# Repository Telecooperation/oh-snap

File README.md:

<h1 align="center">Oh, Snap!</h1>
<p align="center">A Fabrication Pipeline to Magnetically Connect Conventional and 3D-Printed Electronics.</p>

<div align="center">

  <br />
    <!--<a href="https://github.com/othneildrew/Best-README-Template"><strong>Explore the docs »</strong></a>
    <br />
    <br />-->
  <h4 align="center">
    <a href="https://www.youtube.com/watch?v=JX3ZwKnnJVs">Watch Teaser</a>
    ·
    <a href="/assets/Schmitz2021-OhSnap.pdf">View PDF</a>
    ·
    <a href="https://www.youtube.com/watch?v=0AUrrtwaPVQ">Watch Talk</a>
    ·
    <a href="https://doi.org/10.1145/3411764.3445641">Follow DOI</a>
    </h4>
</div>

## Paper Abstract
3D printing has revolutionized rapid prototyping by speeding up the creation of custom-shaped objects. With the rise of multi-material 3D printers, these custom-shaped objects can now be made interactive in a single pass through passive conductive structures. However, connecting conventional electronics to these conductive structures often still requires time-consuming manual assembly involving many wires, soldering or gluing.

To alleviate these shortcomings, we propose <i>Oh, Snap!</i>: a fabrication pipeline and interfacing concept to magnetically connect a 3D-printed object equipped with passive sensing structures to conventional sensing electronics. To this end, <i>Oh, Snap!</i> utilizes ferromagnetic and conductive 3D-printed structures, printable in a single pass on standard printers. We further present a proof-of-concept capacitive sensing board that enables easy and robust magnetic assembly to quickly create interactive 3D-printed objects. We evaluate <i>Oh, Snap!</i> by assessing the robustness and quality of the connection and demonstrate its broad applicability by a series of example applications.

## How to use
We provide the schematics and firmware for the Oh, Snap board for capacitive sensing, as well as sample code and 3D models used for the example applications in the paper.

### Schematics
The [schematics](/schematics/) folder contains all schematics to clone the presented Oh, Snap board or use them as a basis for another kind of board. The schematics are provided in Eagle format.

### Firmware
The [firmware](/firmware/) folder contains the firmware required to operate the Oh, Snap board. Please see [firmware/README.md](/firmware/README.md) for more details on the flashing procedure.

### Example Applications

The [examples](/examples/) folder contains code for some example applications:
- [Car Gesture](examples/gesture) (A)
- [Flowerpot](examples/flowerpot) (B)
- [Smarthome Control](examples/smarthome) (C)
- [Piano](examples/piano)

In addition, it also contains some simple monitoring demos.

### 3D Models
For the 3D models used for the example applications and the evaluation see [here](models/).

## How to cite
Please cite this work like this:
<pre>
  Martin Schmitz, Jan Riemann, Florian Müller, Steffen Kreis, and Max Mühlhäuser. 2021. 
  Oh, Snap! A Fabrication Pipeline to Magnetically Connect Conventional and 3D-Printed Electronics. 
  In Proceedings of the 2021 CHI Conference on Human Factors in Computing Systems (CHI ’21), 1–11. 
  https://doi.org/10.1145/3411764.3445641
  </pre>

or use this

<pre>
@inproceedings{10.1145/3411764.3445641,
author = {Schmitz, Martin and Riemann, Jan and M\"{u}ller, Florian and Kreis, Steffen and M\"{u}hlh\"{a}user, Max},
title = {Oh, Snap! A Fabrication Pipeline to Magnetically Connect Conventional and 3D-Printed Electronics},
year = {2021},
isbn = {9781450380966},
publisher = {Association for Computing Machinery},
address = {New York, NY, USA},
url = {https://doi.org/10.1145/3411764.3445641},
doi = {10.1145/3411764.3445641},
booktitle = {Proceedings of the 2021 CHI Conference on Human Factors in Computing Systems},
articleno = {420},
numpages = {11},
keywords = {capacitive sensing, proximity, touch, prototyping, 3D printing},
location = {Yokohama, Japan},
series = {CHI '21}
}
</pre>

## Credits
This project uses the following sources:
- [Protocentral FDC1004](https://github.com/Protocentral/ProtoCentral_fdc1004_breakout)
- [ESPAsyncWebServer](https://github.com/me-no-dev/ESPAsyncWebServer)
- [MQTT PubSubClient](https://github.com/knolleary/pubsubclient)
- [ArduinoJSON]( https://github.com/bblanchon/ArduinoJson)
- [FreeRTOS]( https://github.com/FreeRTOS/FreeRTOS)
- [Tone.js]( https://github.com/Tonejs/Tone.js)
- [Plotly.js](https://github.com/plotly/plotly.js)
- [Arduino-ESP32](https://github.com/espressif/arduino-esp32)
- [Logo](https://www.pngaaa.com/detail/1826967)

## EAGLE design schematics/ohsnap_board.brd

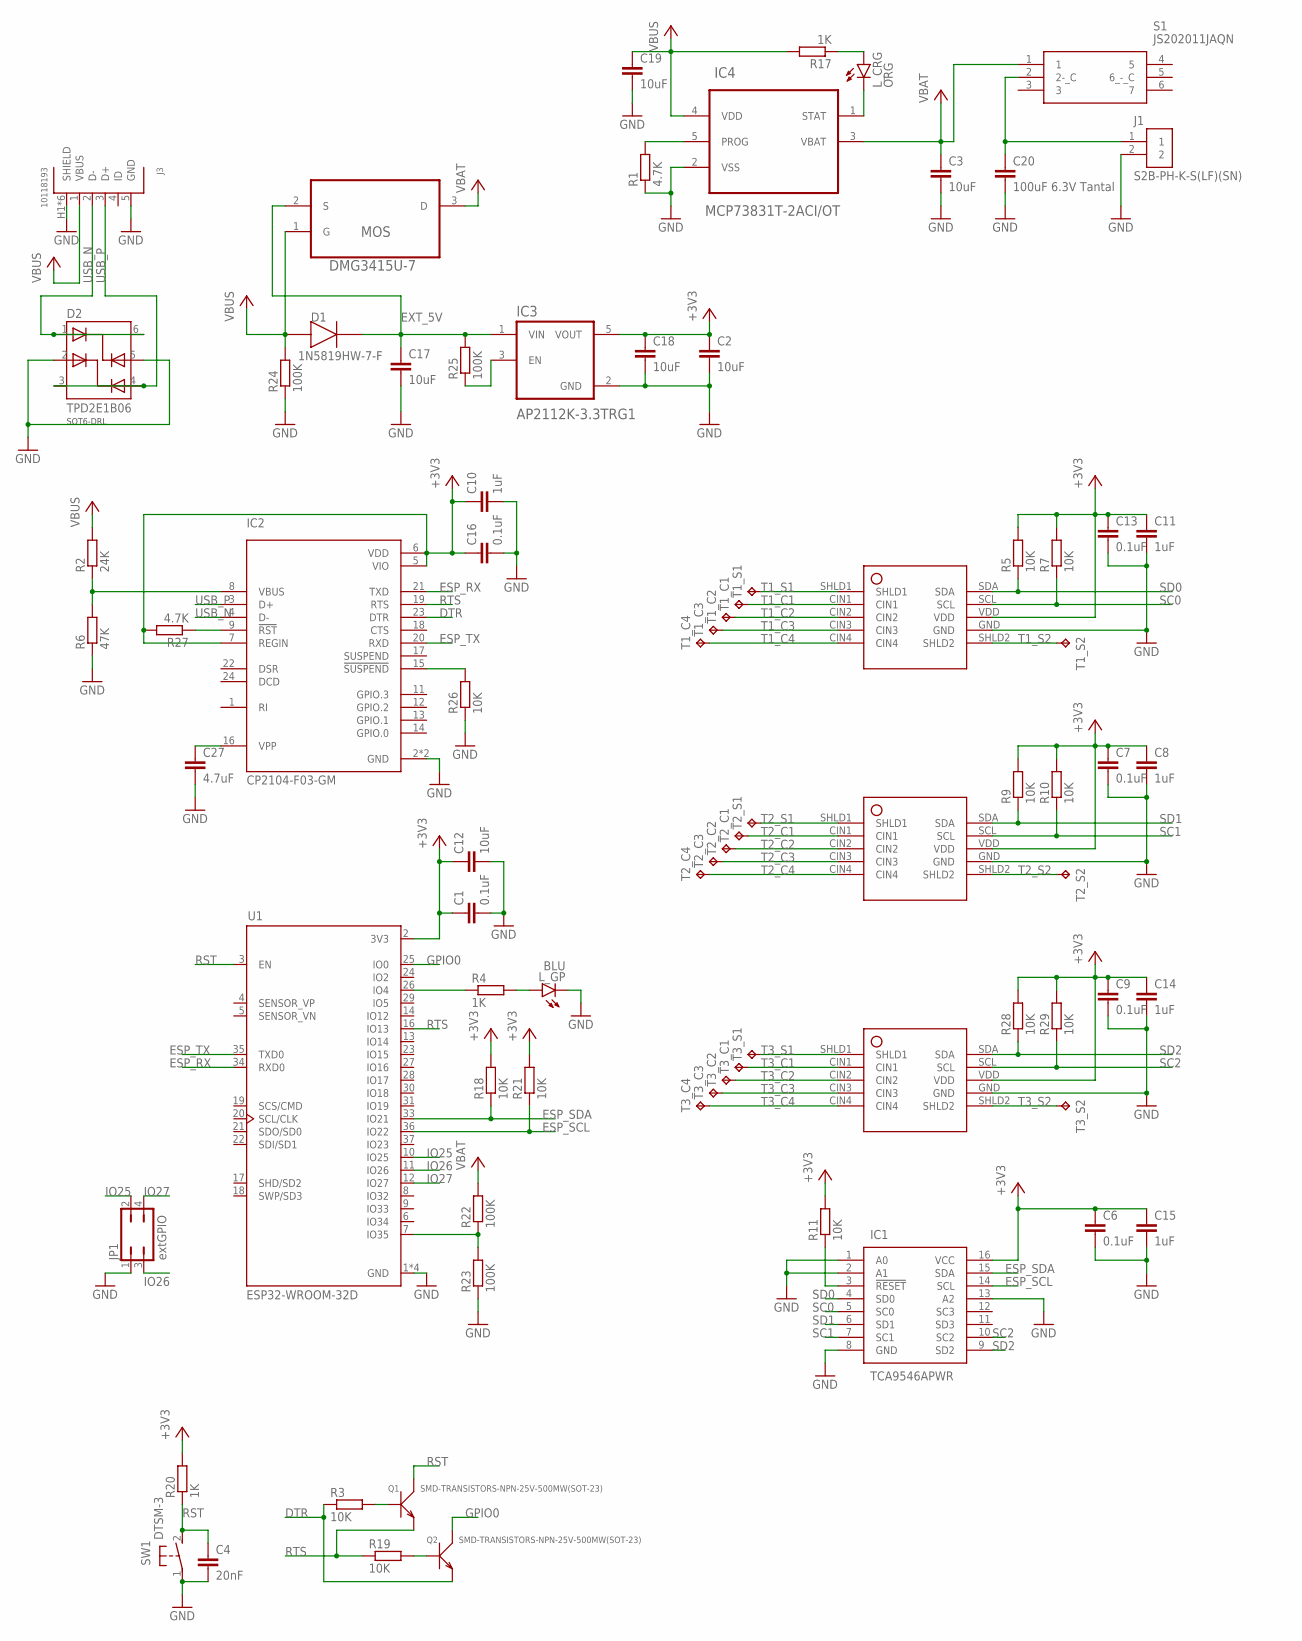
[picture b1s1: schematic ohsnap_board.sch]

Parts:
C1, C6, C7, C9, C13, C16: 0.1uF; C0603
C2, C3, C12, C17, C18, C19: 10uF; C0805
C4: 20nF; C0603
C8, C10, C11, C14, C15: 1uF; C0603
C20: 100uF 6.3V Tantal; C0805
C27: 4.7uF; C0805
D1: 1N5819HW-7-F; SOD370155X135
D2: TPD2E1B06; SOT6-DRL
IC1: TCA9546APWR; SOP65P640X120-16N
IC2: CP2104-F03-GM; QFN50P400X400X80-25N
IC3: AP2112K-3.3TRG1; SOT95P285X140-5N
IC4: MCP73831T-2ACI/OT; SOT95P280X145-5N
IC5, IC6, IC7: FDC1004_SOP10; SOP50P490X109-10N
J1: S2B-PH-K-S(LF)(SN); JST_S2B-PH-K-S(LF)(SN)
J3: 10118193
JP1: extGPIO; JP2Q
L_CRG: ORG; SML0603
L_GP: BLU; SML0603
MOS: DMG3415U-7; SOT95P240X105-3N
Q1, Q2: SMD-TRANSISTORS-NPN-25V-500MW(SOT-23); SOT-23
R1, R27: 4.7K; R0603
R2: 24K; R0603
R3, R5, R7, R9, R10, R11, R18, R19, R21, R26, R28, R29: 10K; R0603
R4, R17, R20: 1K; R0603
R6: 47K; R0603
R22, R23, R24, R25: 100K; R0603
S1: JS202011JAQN
SW1: DTSM-3
T1_C1, T1_C2, T1_C3, T1_C4, T2_C1, T2_C2, T2_C3, T2_C4, T3_C1, T3_C2, T3_C3, T3_C4: TPB2,54; B2,54
T1_S1: T1_S1; B2,54
T1_S2: T1_SHLD2; B2,54
T2_S1: T2_SHLD1; B2,54
T2_S2: T2_SHLD2; B2,54
T3_S1: T3_SHLD1; B2,54
T3_S2: T3_S2; B2,54
U1: ESP32-WROOM-32D; MODULE_ESP32-WROOM-32D

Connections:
+3V3: C1.1, C2.1, C6.1, C7.1, C8.1, C9.1, C10.1, C11.1, C12.1, C13.1, C14.1, C15.1, C16.1, C18.1, IC1.16 (VCC), IC2.5 (VIO), IC2.6 (VDD), IC2.7 (REGIN), IC3.5 (VOUT), IC5.VDD, IC6.VDD, IC7.VDD, R5.2, R7.2, R9.2, R10.2, R11.2, R18.2, R20.2, R21.2, R27.2, R28.2, R29.2, U1.2 (3V3)
DTR: IC2.23 (DTR), Q2.2 (E), R3.1
ESP_RX: IC2.21 (TXD), U1.34 (RXD0)
ESP_SCL: IC1.14 (SCL), R21.1, U1.36 (IO22)
ESP_SDA: IC1.15 (SDA), R18.1, U1.33 (IO21)
ESP_TX: IC2.20 (RXD), U1.35 (TXD0)
EXT_5V: C17.1, D1.1 (C), IC3.1 (VIN), MOS.2 (S), R25.2
GND: C1.2, C2.2, C3.2, C4.2, C6.2, C7.2, C8.2, C9.2, C10.2, C11.2, C12.2, C13.2, C14.2, C15.2, C16.2, C17.2, C18.2, C19.2, C20.2, C27.2, D2.2 (IOB1), D2.5 (IOA2), IC1.1 (A0), IC1.2 (A1), IC1.8 (GND), IC1.13 (A2), IC2.2 (GND), IC2.25 (GND), IC3.2 (GND), IC4.2 (VSS), IC5.GND, IC6.GND, IC7.GND, J1.2, J3.5 (GND), J3.H1 (SHIELD), J3.H2 (SHIELD), J3.S1 (SHIELD), J3.S2 (SHIELD), J3.S3 (SHIELD), J3.S4 (SHIELD), JP1.1, L_GP.C, R1.1, R6.1, R23.1, R24.1, R26.1, SW1.1, U1.1 (GND), U1.15 (GND), U1.38 (GND), U1.39 (GND)
GPIO0: Q2.3 (C), U1.25 (IO0)
IO25: JP1.2, U1.10 (IO25)
IO26: JP1.3, U1.11 (IO26)
IO27: JP1.4, U1.12 (IO27)
unnamed: L_GP.A, R4.2
unnamed: R4.1, U1.26 (IO4)
unnamed: IC3.3 (EN), R25.1
unnamed: R22.1, R23.2, U1.7 (IO35)
unnamed: C20.1, J1.1, S1.2 (2-_C)
unnamed: IC2.15 (!SUSPEND), R26.2
unnamed: C27.1, IC2.16 (VPP)
unnamed: IC2.8 (VBUS), R2.1, R6.2
unnamed: IC2.9 (!RST), R27.1
unnamed: Q1.1 (B), R3.2
unnamed: Q2.1 (B), R19.2
unnamed: IC1.3 (!RESET), R11.1
unnamed: IC4.1 (STAT), L_CRG.C
unnamed: L_CRG.A, R17.1
unnamed: IC4.5 (PROG), R1.2
RST: C4.1, Q1.3 (C), R20.1, SW1.2, U1.3 (EN)
RTS: IC2.19 (RTS), Q1.2 (E), R19.1, U1.16 (IO13)
SC0: IC1.5 (SC0), IC5.SCL, R7.1
SC1: IC1.7 (SC1), IC6.SCL, R10.1
SC2: IC1.10 (SC2), IC7.SCL, R29.1
SD0: IC1.4 (SD0), IC5.SDA, R5.1
SD1: IC1.6 (SD1), IC6.SDA, R9.1
SD2: IC1.9 (SD2), IC7.SDA, R28.1
T1_C1: IC5.CIN1, T1_C1.TP
T1_C2: IC5.CIN2, T1_C2.TP
T1_C3: IC5.CIN3, T1_C3.TP
T1_C4: IC5.CIN4, T1_C4.TP
T1_S1: IC5.SHLD1, T1_S1.TP
T1_S2: IC5.SHLD2, T1_S2.TP
T2_C1: IC6.CIN1, T2_C1.TP
T2_C2: IC6.CIN2, T2_C2.TP
T2_C3: IC6.CIN3, T2_C3.TP
T2_C4: IC6.CIN4, T2_C4.TP
T2_S1: IC6.SHLD1, T2_S1.TP
T2_S2: IC6.SHLD2, T2_S2.TP
T3_C1: IC7.CIN1, T3_C1.TP
T3_C2: IC7.CIN2, T3_C2.TP
T3_C3: IC7.CIN3, T3_C3.TP
T3_C4: IC7.CIN4, T3_C4.TP
T3_S1: IC7.SHLD1, T3_S1.TP
T3_S2: IC7.SHLD2, T3_S2.TP
USB_N: D2.1 (IOA1), D2.6 (NC), IC2.4 (D-), J3.2 (D-)
USB_P: D2.3 (NC), D2.4 (IOB2), IC2.3 (D+), J3.3 (D+)
VBUS: C19.1, D1.2 (A), IC4.4 (VDD), J3.1 (VBUS), MOS.1 (G), R2.2, R17.2, R24.2
VCC: C3.1, IC4.3 (VBAT), MOS.3 (D), R22.2, S1.1

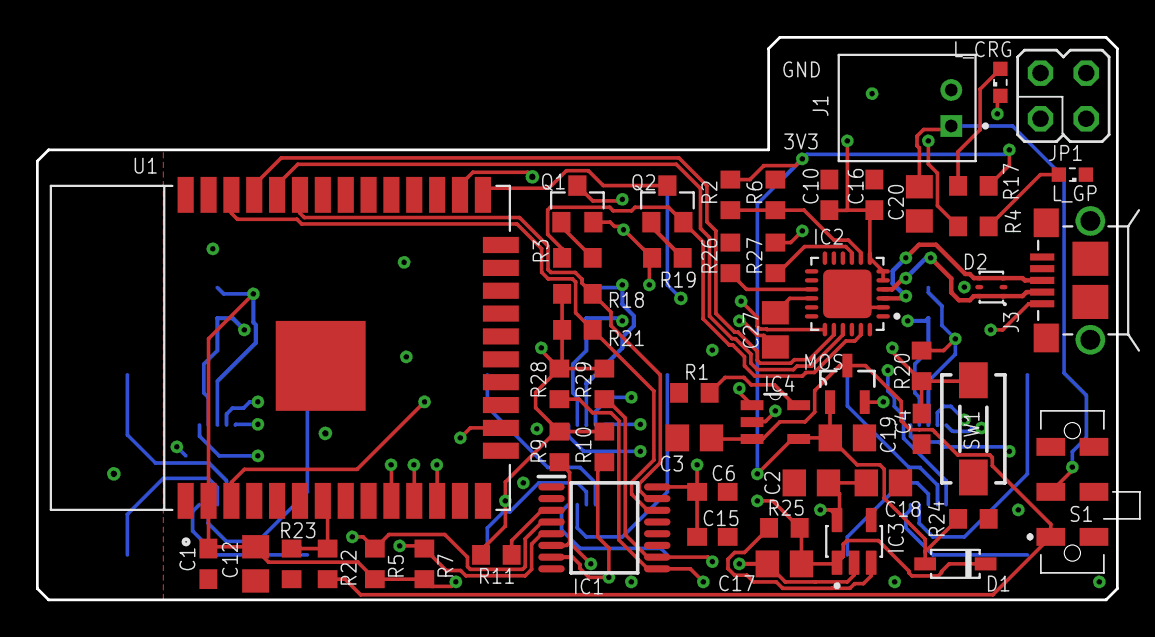
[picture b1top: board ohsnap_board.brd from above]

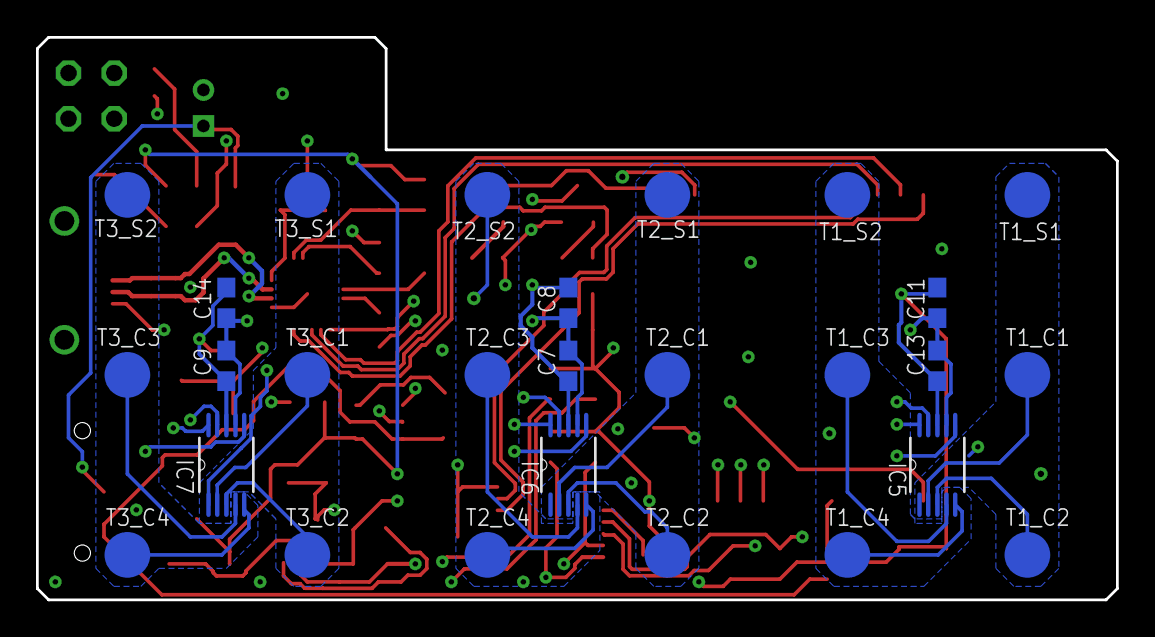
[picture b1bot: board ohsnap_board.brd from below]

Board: 4 copper layers, 60.0 x 31.2 mm, 81 parts (27 on the bottom side), 57 nets.

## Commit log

2021-05-10 Licensing problems
2021-06-11 Added Oh Snap files
2021-06-11 MIT License
2022-04-05 updated bibtex
